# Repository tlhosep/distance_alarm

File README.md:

# Distance alarm using pi pico
Measure distances using raspberry pi pico

This project aims to support you in building a simple measuring application.

You need these components:

* Raspberry pi pico or better
* A power source, eg. 12V battery
* HC-SR04-P sensor
* 12v led or equivalent
* 1 npn transistor
* 1 2k2 resistor
* 2 10k resitors
* step-down regulator to convert to 5V
* 1602 HD44780 display with I2C connector or board
* some soldering equipment
* for the housing a 3D printer

The prototype looked like this:

The alarm in operation looks like this:

The top LED is dimmed when distance gets greater, the lower LED indicates "in operation". The housings sit on a 12V battery, you could definetly use a one with lower capacity (!). Left to the LEDs you see a motion detector to turn on the power, so not always power is consumed. On top of that a display shows the capacity of the battery.

The distance sensor could be found on the lower end, fixed by tape on the IKEA shelf :) 

This is my layout, using mostly components that I had at hand:

Soldered end:

In my little laboratoy it looked like this showing the two possible information:

The temp is only shown occasionally...

But the setup distance/alarm (use the poti to set this up) shows in most cases:

The schema and a pcb layout that may help you solder it (!not perfect, do not print!) could be found in the kicad folder.

The stl and FCStd files are located in the freecad folder besides the box I used for the sensor and the original box for the display.

Please use thonny to test the application and your setup.

## Be careful
If you unsolder the pins from the HC-SR04-P sensor, make sure to solder a connection between the two layers. If you only connect to one layer some signals may get lost...

## About the housing
The housing for the lcd display should be rotated by 180° to show the info in the right direction. As I did not want to print the housing again, I simpoly rotated the whole housing...

The distance for the step-down pcb could be made a little bit wider...

## About the pcb
Th connector to the lcd is somehow wrong connected, not 1:1. Please be careful when you connect the display via I2C and use the right pins.

Do **not** use the pcp to print your board. Do only hard-wiring as I did or enhance the layout!

## About the LED
The 12v led is connected to the NPN Transistor. If you will use different LED-types, the transistor may not be needed.

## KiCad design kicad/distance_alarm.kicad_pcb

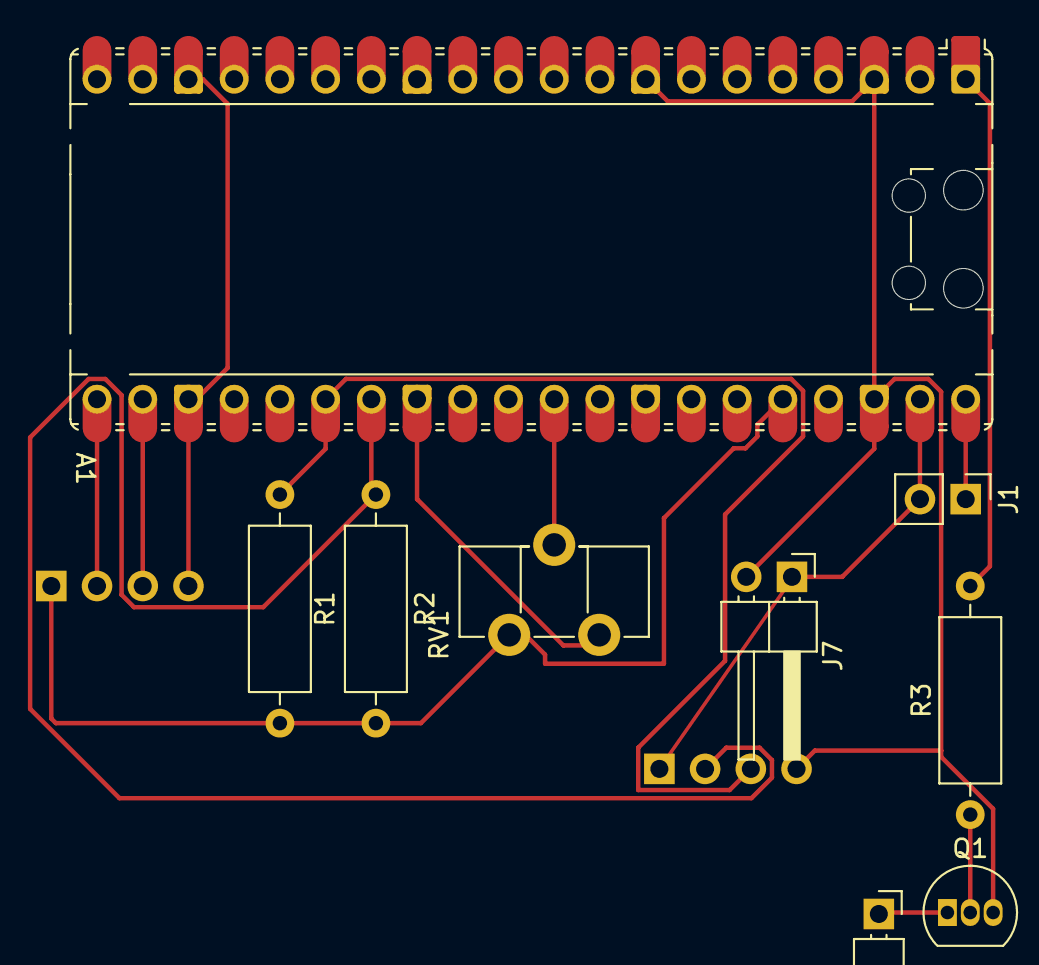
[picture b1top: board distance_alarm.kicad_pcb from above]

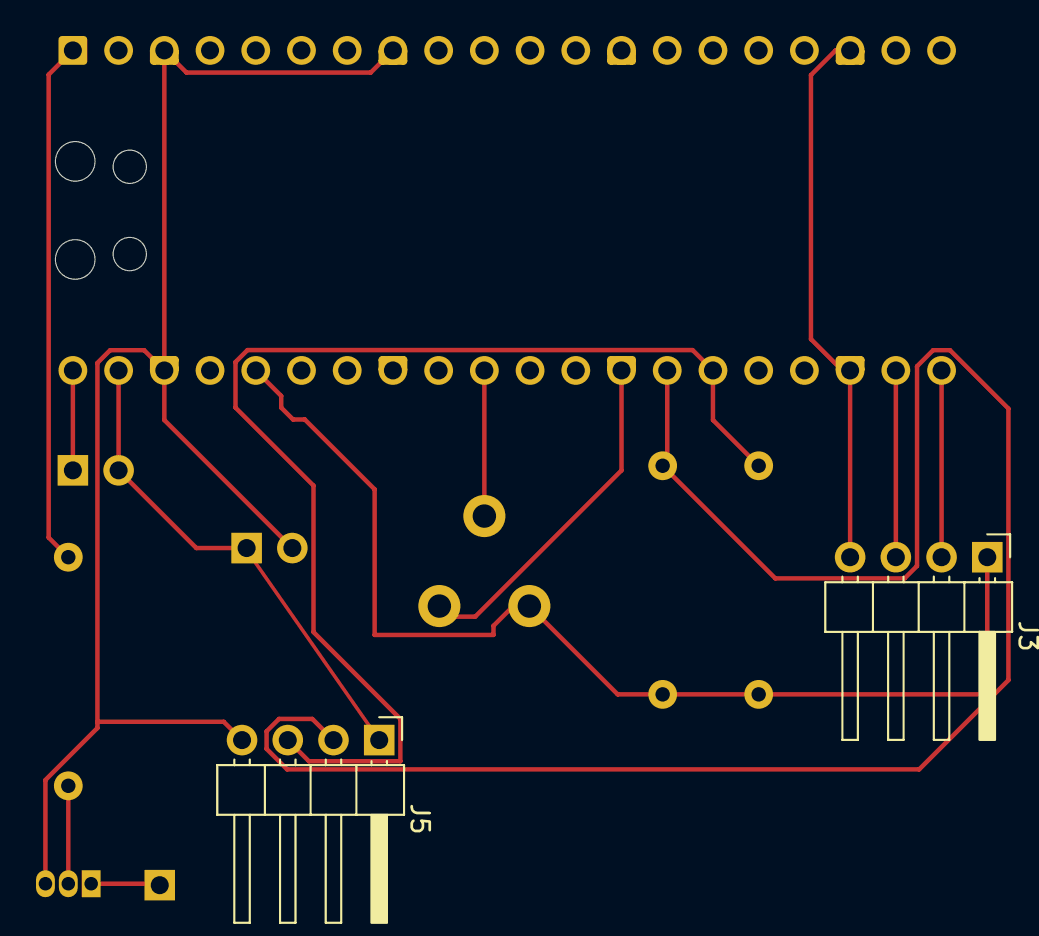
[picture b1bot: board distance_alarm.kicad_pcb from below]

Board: 2 copper layers, 11 parts (2 on the bottom side), 12 nets.

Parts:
A1: RaspberryPi_Pico; RaspberryPi_Pico_Common_Unspecified
J1: Conn_01x02; PinHeader_1x02_P2.54mm_Vertical
J3, J5: Conn_01x04; PinHeader_1x04_P2.54mm_Horizontal
J7: Conn_01x02; PinHeader_1x02_P2.54mm_Horizontal
J8: Conn_01x01_Pin; PinHeader_1x01_P2.54mm_Horizontal
Q1: BC237; TO-92_Inline
R1, R2: 10k; R_Axial_DIN0309_L9.0mm_D3.2mm_P12.70mm_Horizontal
R3: 2k2; R_Axial_DIN0309_L9.0mm_D3.2mm_P12.70mm_Horizontal
RV1: 10k; Potentiometer_Piher_PT-10-H05_Horizontal

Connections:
+3.3V: A1.36 (3V3), J3.1, R1.2, R2.2, RV1.1
+5V: A1.39 (VSYS), J1.2, J5.1, J7.1
GND: A1.3 (GND), A1.8 (GND), A1.13 (GND), A1.18 (GND), A1.23 (GND), A1.28 (GND), A1.38 (GND), J3.4, J5.4, J7.2, Q1.3 (E), RV1.3
unnamed: A1.1 (GPIO0), R3.2
unnamed: A1.21 (GPIO16), J3.2
unnamed: A1.22 (GPIO17), J3.3
unnamed: A1.26 (GPIO20), J5.3, R1.1
unnamed: A1.27 (GPIO21), J5.2, R2.1
unnamed: A1.31 (GPIO26_ADC0), RV1.2
unnamed: A1.40 (VBUS), J1.1
unnamed: J8.1, Q1.1 (C)
unnamed: Q1.2 (B), R3.1

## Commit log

2025-04-26 Inital population with an early version
2025-05-04 Working application
2025-05-05 updated version, now showing a bar
2025-05-07 Updated version, no longer blinking but dimmed
2025-05-08 Little amendments
